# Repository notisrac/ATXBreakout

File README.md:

# ATX breakout board

Breakout board for the 24pin [ATX](https://en.wikipedia.org/wiki/ATX) connector.

I use it to turn an old ATX [PSU](https://en.wikipedia.org/wiki/Power_supply_unit_(computer)) into a bench power supply.

## Features
* 3.3v, 5v, 12v, -12v
* All of the outputs are fused
* Connector for the PSU on button
* Connector for power on and power ok leds
* Connector for an ammeter
* Extra 5v connectors for misc stuff
* Connector for standby 5v
* Rated for 10amps per rail

## Similar, commercially available products
* Seeed Studio: [http://www.seeedstudio.com/depot/ATX-breakout-board-bench-power-supply-p-1222.html](http://www.seeedstudio.com/depot/ATX-breakout-board-bench-power-supply-p-1222.html)
* Sparkfun: [https://www.sparkfun.com/products/retired/9558](https://www.sparkfun.com/products/retired/9558)

## Pictures

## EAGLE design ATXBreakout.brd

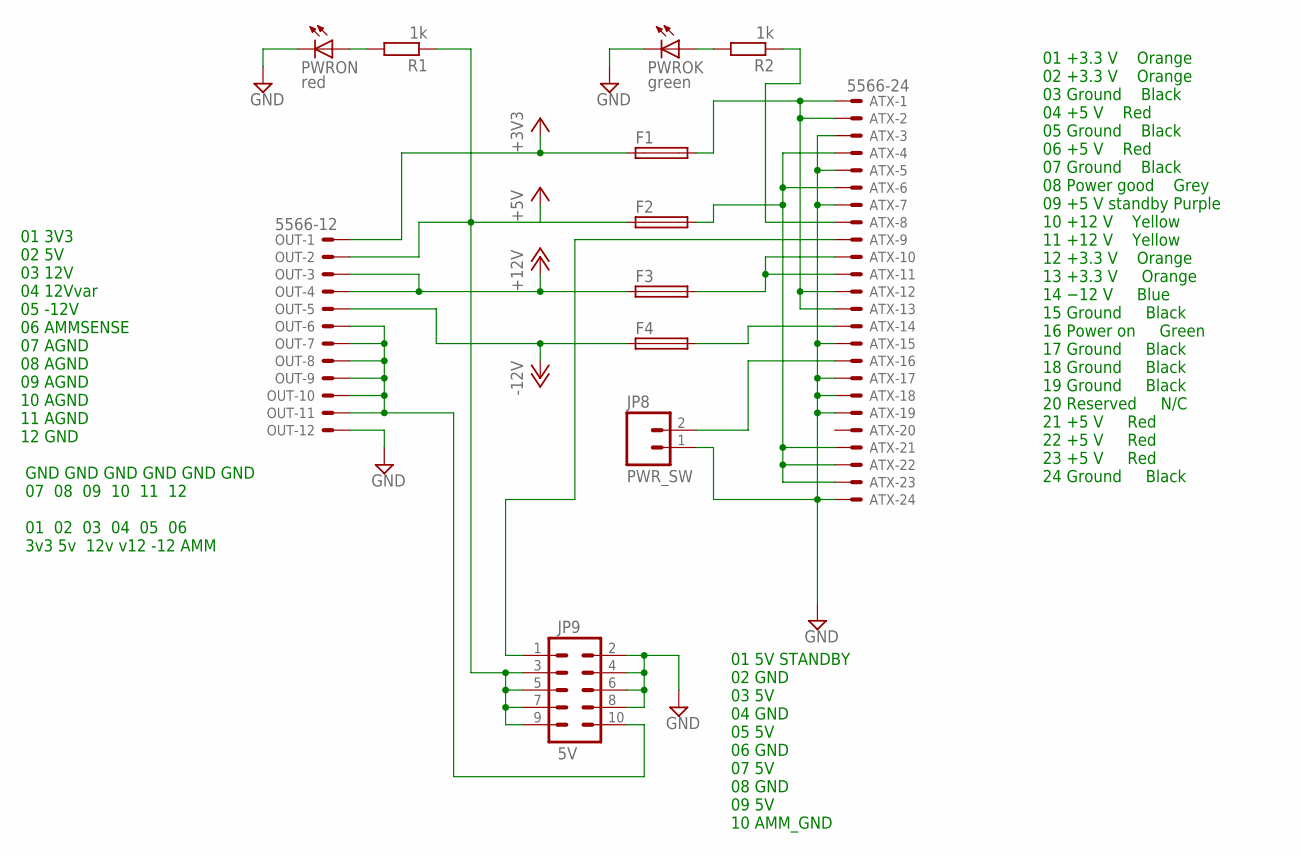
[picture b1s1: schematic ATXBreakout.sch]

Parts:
ATX: 5566-24
F1, F2, F3, F4: FUSESHK20Q; SHK20Q
JP8: PWR_SW; 1X02
JP9: 5V; AVR_ICSP
OUT: 5566-12
PWROK: green; LED5MM
PWRON: red; LED5MM
R1, R2: 1k; 0204/7

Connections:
+3V3: F1.1A (1), OUT.1
+5V: F2.1A (1), JP9.3, JP9.5, JP9.7, JP9.9, OUT.2, R1.1
+12V: F3.1A (1), OUT.3, OUT.4
-12V: F4.1A (1), OUT.5
GND: ATX.3, ATX.5, ATX.7, ATX.15, ATX.17, ATX.18, ATX.19, ATX.24, JP8.1, JP9.2, JP9.4, JP9.6, JP9.8, OUT.12, PWROK.K (C), PWRON.K (C)
unnamed: ATX.1, ATX.2, ATX.12, ATX.13, F1.2A (2)
unnamed: ATX.4, ATX.6, ATX.21, ATX.22, ATX.23, F2.2A (2)
unnamed: ATX.10, ATX.11, F3.2A (2)
unnamed: ATX.14, F4.2A (2)
unnamed: PWRON.A, R1.2
unnamed: ATX.16, JP8.2
unnamed: PWROK.A, R2.2
unnamed: ATX.8, R2.1
unnamed: JP9.10, OUT.6, OUT.7, OUT.8, OUT.9, OUT.10, OUT.11
unnamed: ATX.9, JP9.1

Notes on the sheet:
01 +3.3 V Orange 02 +3.3 V Orange 03 Ground Black 04 +5 V Red 05 Ground Black 06 +5 V Red 07 Ground Black 08 Power good Grey 09 +5 V standby Purple 10 +12 V Yellow 11 +12 V Yellow 12 +3.3 V Orange 13 +3.3 V Orange 14 −12 V Blue 15 Ground Black 16 Power on Green 17 Ground Black 18 Ground Black 19 Gr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
01 3V3 02 5V 03 12V 04 12Vvar 05 -12V 06 AMMSENSE 07 AGND 08 AGND 09 AGND 10 AGND 11 AGND 12 GND GND GND GND GND GND GND 07 08 09 10 11 12 01 02 03 04 05 06 3v3 5v 12v v12 -12 AMM
01 5V STANDBY 02 GND 03 5V 04 GND 05 5V 06 GND 07 5V 08 GND 09 5V 10 AMM_GND

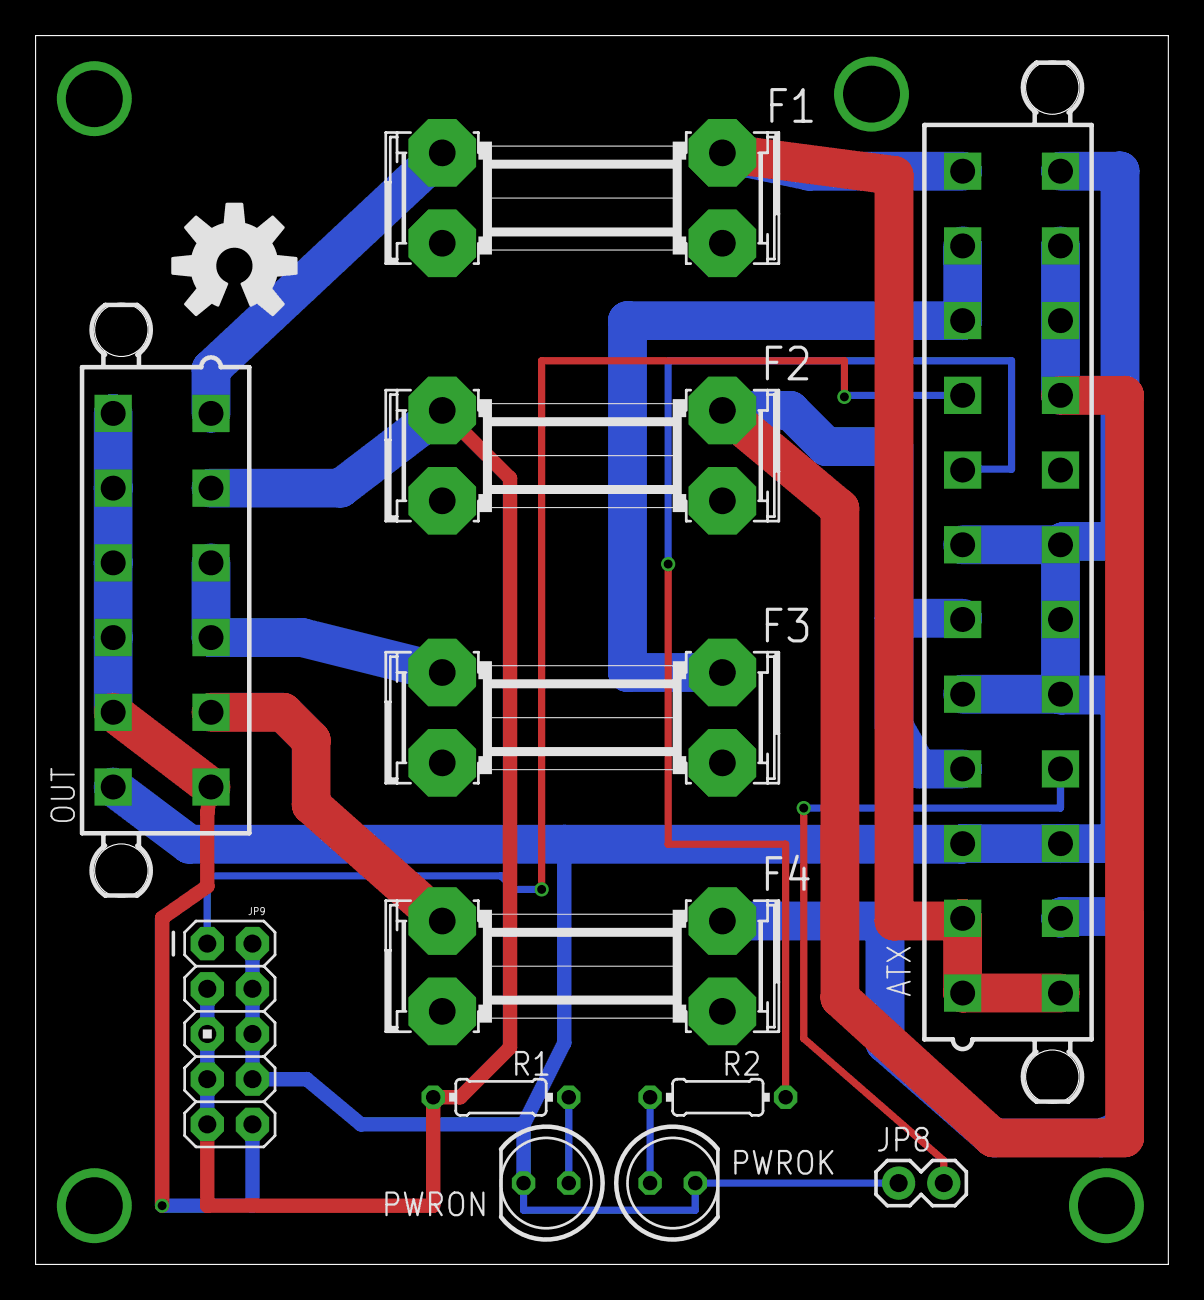
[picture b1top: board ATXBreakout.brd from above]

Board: 2 copper layers, 63.7 x 69.1 mm, 13 parts (0 on the bottom side), 15 nets.

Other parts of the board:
U$1: OSHW-LOGO-L

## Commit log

2016-02-07 - Fixed: README.md had a missing closing bracket.
2018-07-27 Fixed README issues
2018-07-28 Added GA beacon to the README
2018-07-29 Removed epf file

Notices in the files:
parts and their libraries:
SparkFun-Connectors: Licensing: Creative Commons ShareAlike 4.0 International - https://creativecommons.org/licenses/by-sa/4.0
